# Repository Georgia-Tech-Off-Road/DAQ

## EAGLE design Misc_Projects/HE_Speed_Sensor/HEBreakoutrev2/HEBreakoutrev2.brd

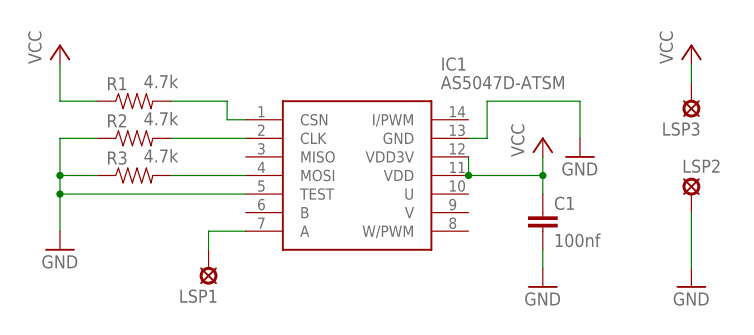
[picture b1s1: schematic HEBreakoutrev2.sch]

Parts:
C1: 100nf; 0603-CAP
IC1: AS5047D-ATSM; SOP65P640X120-14N
LSP1, LSP2, LSP3: LSP10
R1, R2, R3: 4.7k; 0603-RES

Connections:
GND: C1.2, IC1.5 (TEST), IC1.13 (GND), LSP2.MP, R2.1, R3.1
unnamed: IC1.1 (CSN), R1.2
unnamed: IC1.2 (CLK), R2.2
unnamed: IC1.4 (MOSI), R3.2
unnamed: IC1.7 (A), LSP1.MP
VCC: C1.1, IC1.11 (VDD), IC1.12 (VDD3V), LSP3.MP, R1.1

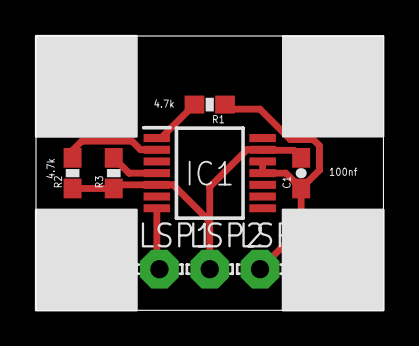
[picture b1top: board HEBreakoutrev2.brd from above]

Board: 2 copper layers, 19.3 x 15.2 mm, 8 parts (0 on the bottom side), 6 nets.

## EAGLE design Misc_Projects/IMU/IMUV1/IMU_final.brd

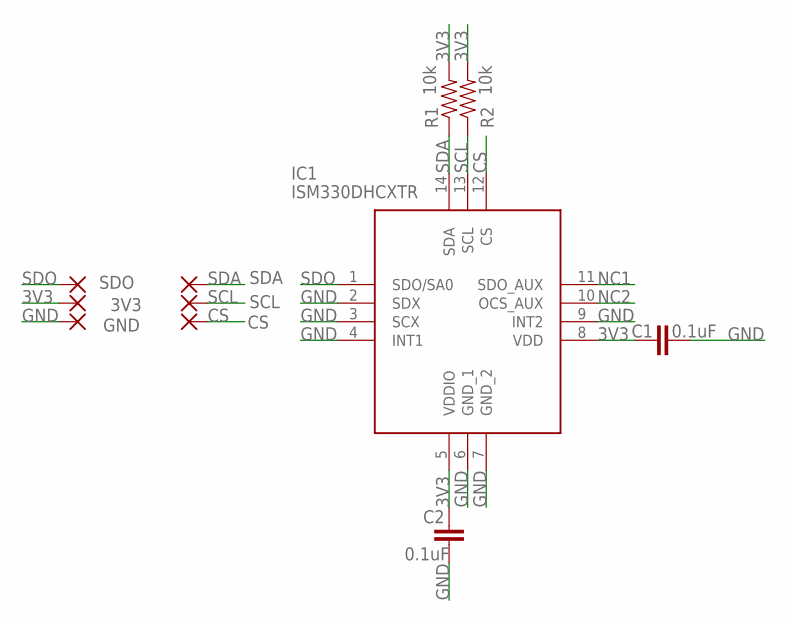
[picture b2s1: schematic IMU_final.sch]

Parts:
3V3: SMD5; SMD2,54-5,08
C1, C2: 0.1uF; 0603
CS: SMD5; SMD2,54-5,08
GND: SMD5; SMD2,54-5,08
IC1: ISM330DHCXTR; LGA-14(2.5X3X0.86)
R1, R2: 10k; 0603
SCL: SMD5; SMD2,54-5,08
SDA: SMD5; SMD2,54-5,08
SDO: SMD5; SMD2,54-5,08

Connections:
3V3: 3V3.1, C1.1, C2.1, IC1.5 (VDDIO), IC1.8 (VDD), R1.2, R2.2
CS: CS.1, IC1.12 (CS)
GND: C1.2, C2.2, GND.1, IC1.2 (SDX), IC1.3 (SCX), IC1.4 (INT1), IC1.6 (GND_1), IC1.7 (GND_2), IC1.9 (INT2)
NC1: IC1.11 (SDO_AUX)
NC2: IC1.10 (OCS_AUX)
SCL: IC1.13 (SCL), R2.1, SCL.1
SDA: IC1.14 (SDA), R1.1, SDA.1
SDO: IC1.1 (SDO/SA0), SDO.1

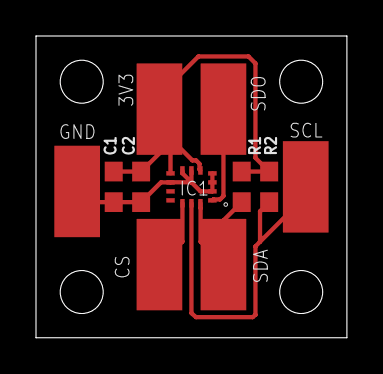
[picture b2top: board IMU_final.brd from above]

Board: 2 copper layers, 17.3 x 16.8 mm, 11 parts (0 on the bottom side), 6 nets.

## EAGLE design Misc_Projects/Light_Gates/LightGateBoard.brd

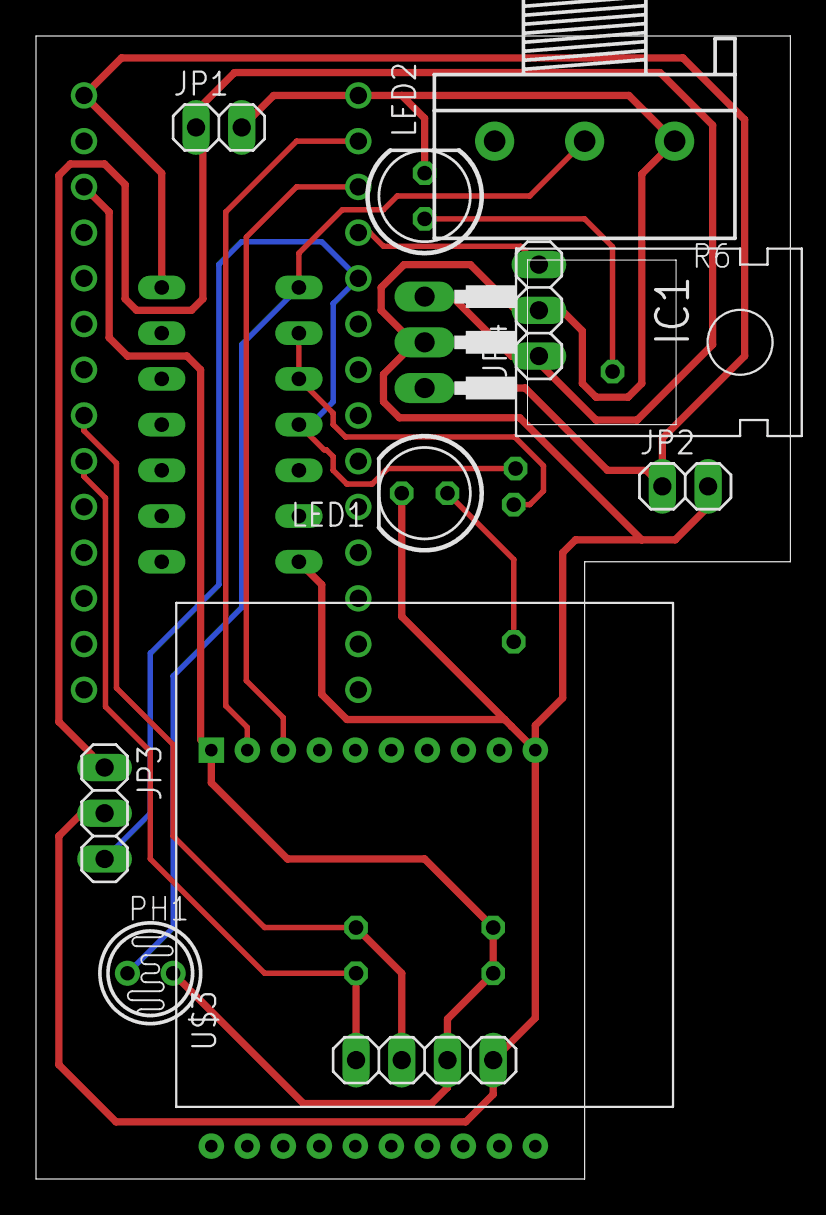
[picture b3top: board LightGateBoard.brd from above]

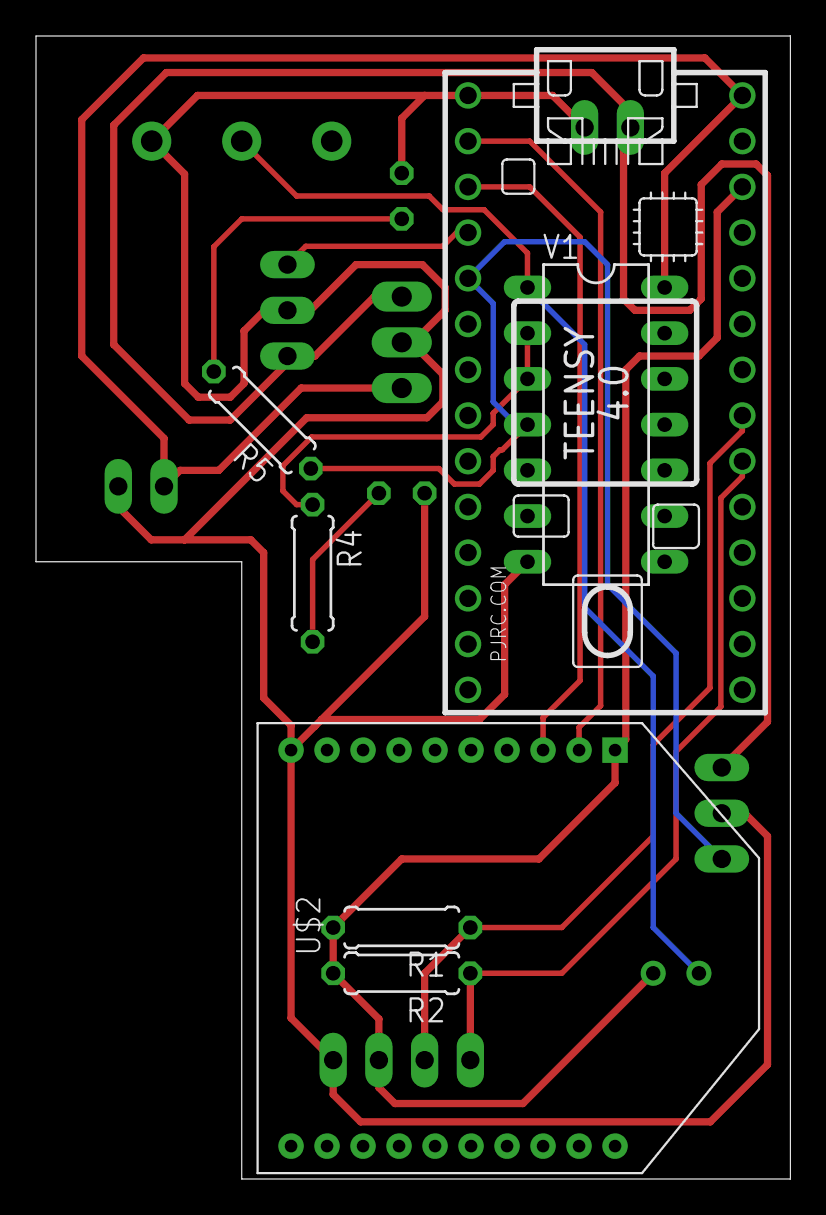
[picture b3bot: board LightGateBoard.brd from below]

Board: 2 copper layers, 41.9 x 63.5 mm, 17 parts (7 on the bottom side), 14 nets.

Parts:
IC1: TO-220-H
JP1, JP2: 1X02
JP3, JP4: 1X03
LED1: Green; LED-5MM
LED2: Red; LED-5MM
PH1: PHOTORESISTOR0N1; TO46-VT200
R1, R2: 10k; 1/4W-0.3
R4, R5: 220; 1/4W-0.3
R6: 3RP/1610N
U$1: TEENSY_4.0_SIMPLE
U$2: XBEE
U$3: OLED_SSD1306
V1: LOGIC_HEX_INVERTER_7404N; DIL14

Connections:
3V3: PH1.1, R1.2, R2.2, U$1.3V3_LO, U$2.1, U$3.VCC
5V: IC1.3, JP2.1, U$1.VIN, V1.14
GND: IC1.2, JP1.2, JP2.2, JP3.2, JP4.2, LED1.K, LED2.K, R6.1, U$1.GND, U$2.10, U$3.GND, V1.7
unnamed: LED1.A, R4.2
unnamed: LED2.A, R5.2
NSIG: R4.1, V1.2, V1.3
RX: U$1.0/RX, U$2.2
SCL: R1.1, U$1.19/A5/SCL, U$3.SCL
SDA: R2.1, U$1.18/A4/SDA, U$3.SDA
SIG: PH1.2, R6.2, V1.1
SIG_END: JP3.3, R5.1, U$1.3/CANTX, V1.4
SIG_START: JP4.3, U$1.2
TX: U$1.1/TX, U$2.3
VCC: IC1.1, JP1.1, JP3.1, JP4.1

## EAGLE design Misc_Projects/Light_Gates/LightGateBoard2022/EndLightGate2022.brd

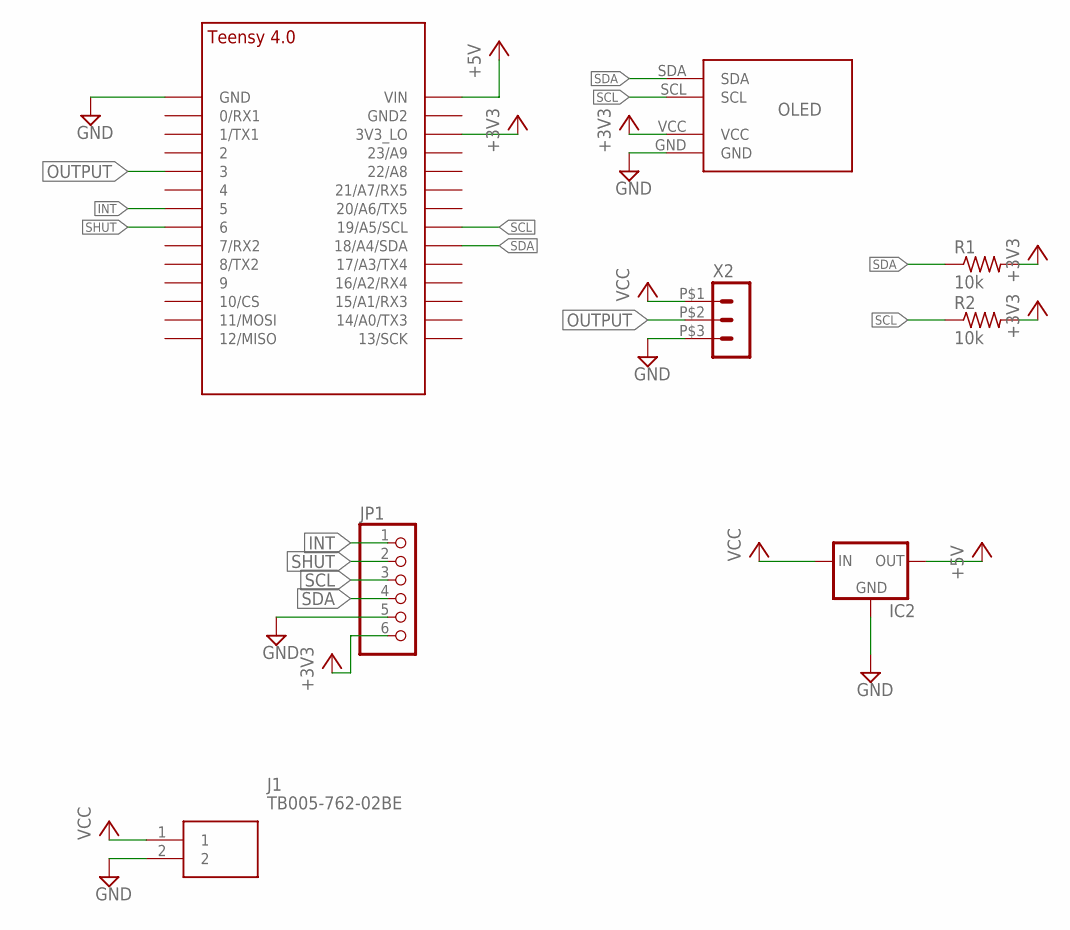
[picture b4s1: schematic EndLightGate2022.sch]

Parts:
IC2: REG_5V_L7805_HOR; TO-220-H
J1: TB005-762-02BE; TB00576202BE
JP1: PINHD-1X6; 1X06
R1, R2: 10k; 1/4W-0.4
U$1: TEENSY_4.0_SIMPLE
U$2: OLED_SSD1306
X2: HEADER_POS3_43650-0300; 43650-0300

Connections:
+3V3: JP1.6, R1.2, R2.2, U$1.3V3_LO, U$2.VCC
+5V: IC2.3 (OUT), U$1.VIN
GND: IC2.2 (GND), J1.2, JP1.5, U$1.GND, U$2.GND, X2.P$3 (3)
INT: JP1.1, U$1.5
OUTPUT: U$1.3/CANTX (3), X2.P$2 (2)
SCL: JP1.3, R2.1, U$1.19/A5/SCL, U$2.SCL
SDA: JP1.4, R1.1, U$1.18/A4/SDA, U$2.SDA
SHUT: JP1.2, U$1.6
VCC: IC2.1 (IN), J1.1, X2.P$1 (1)

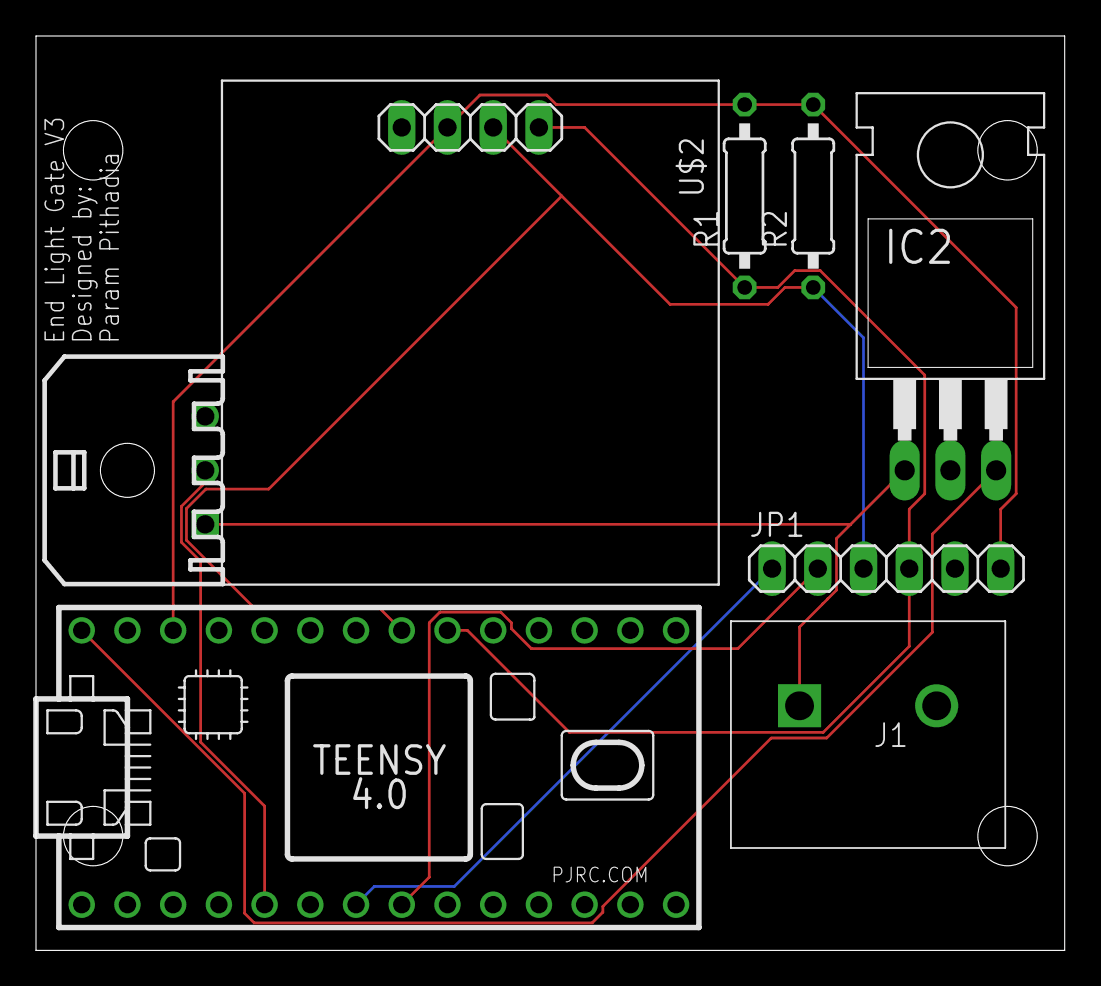
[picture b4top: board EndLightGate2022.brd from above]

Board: 2 copper layers, 57.1 x 50.8 mm, 8 parts (0 on the bottom side), 9 nets.

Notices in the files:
parts and their libraries:
SparkFun-Capacitors: Licensing: Creative Commons ShareAlike 4.0 International - https://creativecommons.org/licenses/by-sa/4.0
